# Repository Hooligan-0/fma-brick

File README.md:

# fma-brick
A custom internet router for WiFi experiments

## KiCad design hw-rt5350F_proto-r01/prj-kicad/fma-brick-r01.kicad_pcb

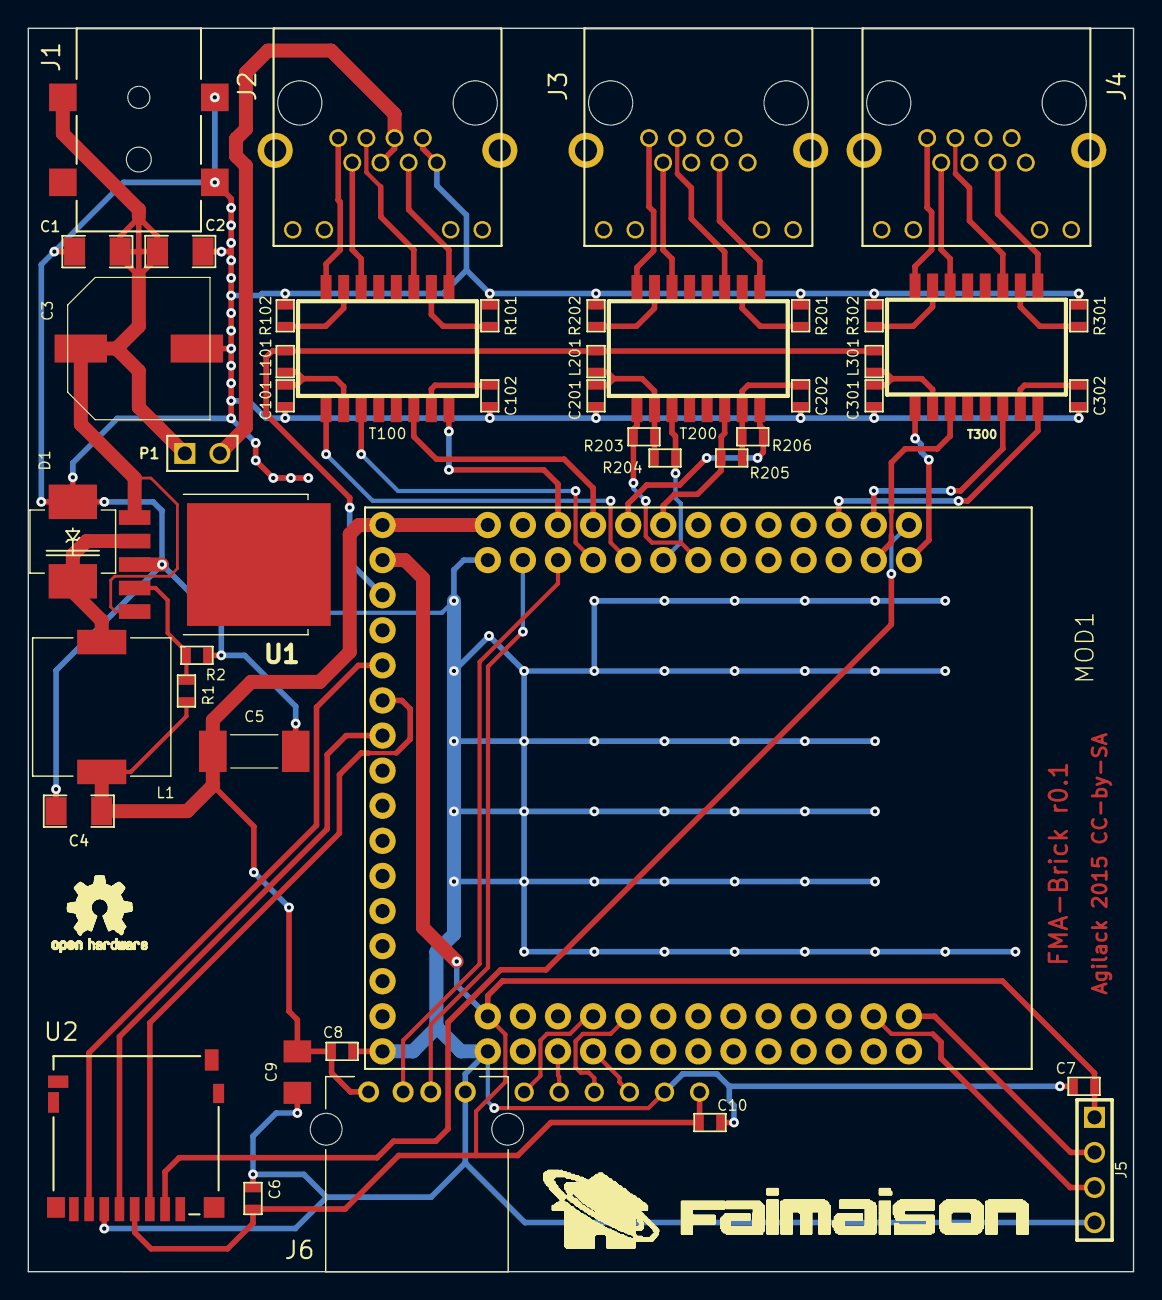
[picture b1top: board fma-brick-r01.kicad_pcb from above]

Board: 2 copper layers, 80.0 x 90.0 mm, 54 parts (0 on the bottom side), 56 nets.

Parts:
C1, C2: 10uF; SMD1206
C3: 33uF; C_EEE_G
C4: C; SMD1206
C5: CP; C_TAJD
C6, C7, C8, C10: 1uF; SMD0603
C9: 47uF; C_TAJB
C101, C102, C201, C202, C301, C302: 100nF; SMD0603
D1: B560; DO214AB
J1: CONN_DC10A-2.1; CONN_DC-694106106102
J2, J3, J4: CONN_RJ45-L; CONN_AJT34L-881x
J5: CONN_4
J6: CONN_USB_A; CONN_61400416021
L1: 47uH; I_MSS1048
L101, L201, L301: FB100; SMD0603
MOD1: MOD-RT5350F
P1: JUMPER; CONN_2
R1, R2: R; SMD0603
R101, R102, R201, R202, R301, R302: 75; SMD0603
R203, R204, R205, R206: 49.9; SMD0603
T100, T200, T300: TRANSFORMER_1:1; TR_W749013011
TP1, TP2, TP3, TP4, TP5, TP6: CONN_1; TP_PIN
U1: LM2596; SMD_DPAK
U2: CONN_USD; CONN_114-00841-68
fma_logo: VAL**; fma_logo
ohw_logo: VAL**; ohw_logo

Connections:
+1.8V: L101.1, L201.1, L301.1, MOD1.55
+3.3V: C6.1, C7.1, C10.1, J5.1, MOD1.1, MOD1.54, TP1.1, U2.4
+5V: C4.1, C5.1, C8.1, C9.1, J6.4, L1.2, MOD1.27, MOD1.53, R1.1
+Vin: C1.1, C2.1, C3.1, J1.2, P1.1, U1.1, U1.5
+Vpoe: J2.4, J2.5, P1.2
GND: C1.2, C2.2, C3.2, C4.2, C5.2, C6.2, C7.2, C8.2, C9.2, C10.2, C101.2, C102.2, C201.2, C202.2, C301.2, C302.2, D1.1, J1.1, J2.7, J2.8, J5.4, J6.1, MOD1.2, MOD1.28, MOD1.68, R2.2, R101.1, R102.2, R201.1, R202.2, R301.1, R302.2, TP2.1, U1.3, U2.6
JTAG_TCK: MOD1.8, TP3.1
JTAG_TDI: MOD1.6, TP5.1
JTAG_TDO: MOD1.9, TP4.1
JTAG_TMS: MOD1.7, TP6.1
unnamed: R302.1, T300.15
unnamed: R201.2, T200.10
unnamed: R202.1, T200.15
unnamed: R301.2, T300.10
unnamed: C202.1, R205.1, R206.2, T200.7
unnamed: C201.1, L201.2, R203.1, R204.2, T200.2
unnamed: J4.6, T300.9
unnamed: C302.1, T300.7
unnamed: C301.1, L301.2, T300.2
unnamed: R1.2, R2.1, U1.4
unnamed: D1.2, L1.1, U1.2
unnamed: J2.2, T100.14
unnamed: C101.1, L101.2, T100.2
unnamed: J2.6, T100.9
unnamed: R101.2, T100.10
unnamed: J2.3, T100.11
unnamed: R102.1, T100.15
unnamed: J2.1, T100.16
unnamed: J3.6, T200.9
unnamed: J3.3, T200.11
unnamed: J4.3, T300.11
unnamed: J4.2, T300.14
unnamed: J4.1, T300.16
unnamed: J3.1, T200.16
unnamed: J3.2, T200.14
unnamed: C102.1, T100.7
RX0_N: MOD1.47, T300.8
RX0_P: MOD1.49, T300.6
RX3_N: MOD1.35, R206.1, T200.8
RX3_P: MOD1.37, R205.2, T200.6
RX4_N: MOD1.31, T100.8
RX4_P: MOD1.33, T100.6
SPI_CLK: MOD1.59, U2.5
SPI_CS: MOD1.51, U2.2
SPI_MISO: MOD1.57, U2.7
SPI_MOSI: MOD1.58, U2.3
TX0_N: MOD1.50, T300.3
TX0_P: MOD1.52, T300.1
TX3_N: MOD1.38, R204.1, T200.3
TX3_P: MOD1.40, R203.2, T200.1
TX4_N: MOD1.34, T100.3
TX4_P: MOD1.36, T100.1
UART_RX: J5.2, MOD1.25
UART_TX: J5.3, MOD1.23
USB_DM: J6.2, MOD1.30
USB_DP: J6.3, MOD1.32

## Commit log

2015-06-11 = ADD: Initial commit of router prototype based on RT5350F module
2015-06-11 = ADD: export top layer for footprint validation
2015-06-12 = UPD: Design of rev0.1 is complete and ready for verify
2015-06-15 = ADD: Generate production files

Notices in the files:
hw-rt5350F_proto-r01/prj-kicad/fma-brick-r01.kicad_pcb:
Agilack 2015 CC-by-SA
